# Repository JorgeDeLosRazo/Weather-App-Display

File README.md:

# Weather App Display

### Materials
- Adafruit HUZZAH32 (ESP32 feather)
- 3.7" 416x240 Monochrome Black/White eInk / ePaper - Bare Display (UC8253 Chipset)
- Adafruit eInk Breakout Friend with 32KB SRAM
- 5V 1A phone charger (to connect HUZZAH32 to wall outlet)

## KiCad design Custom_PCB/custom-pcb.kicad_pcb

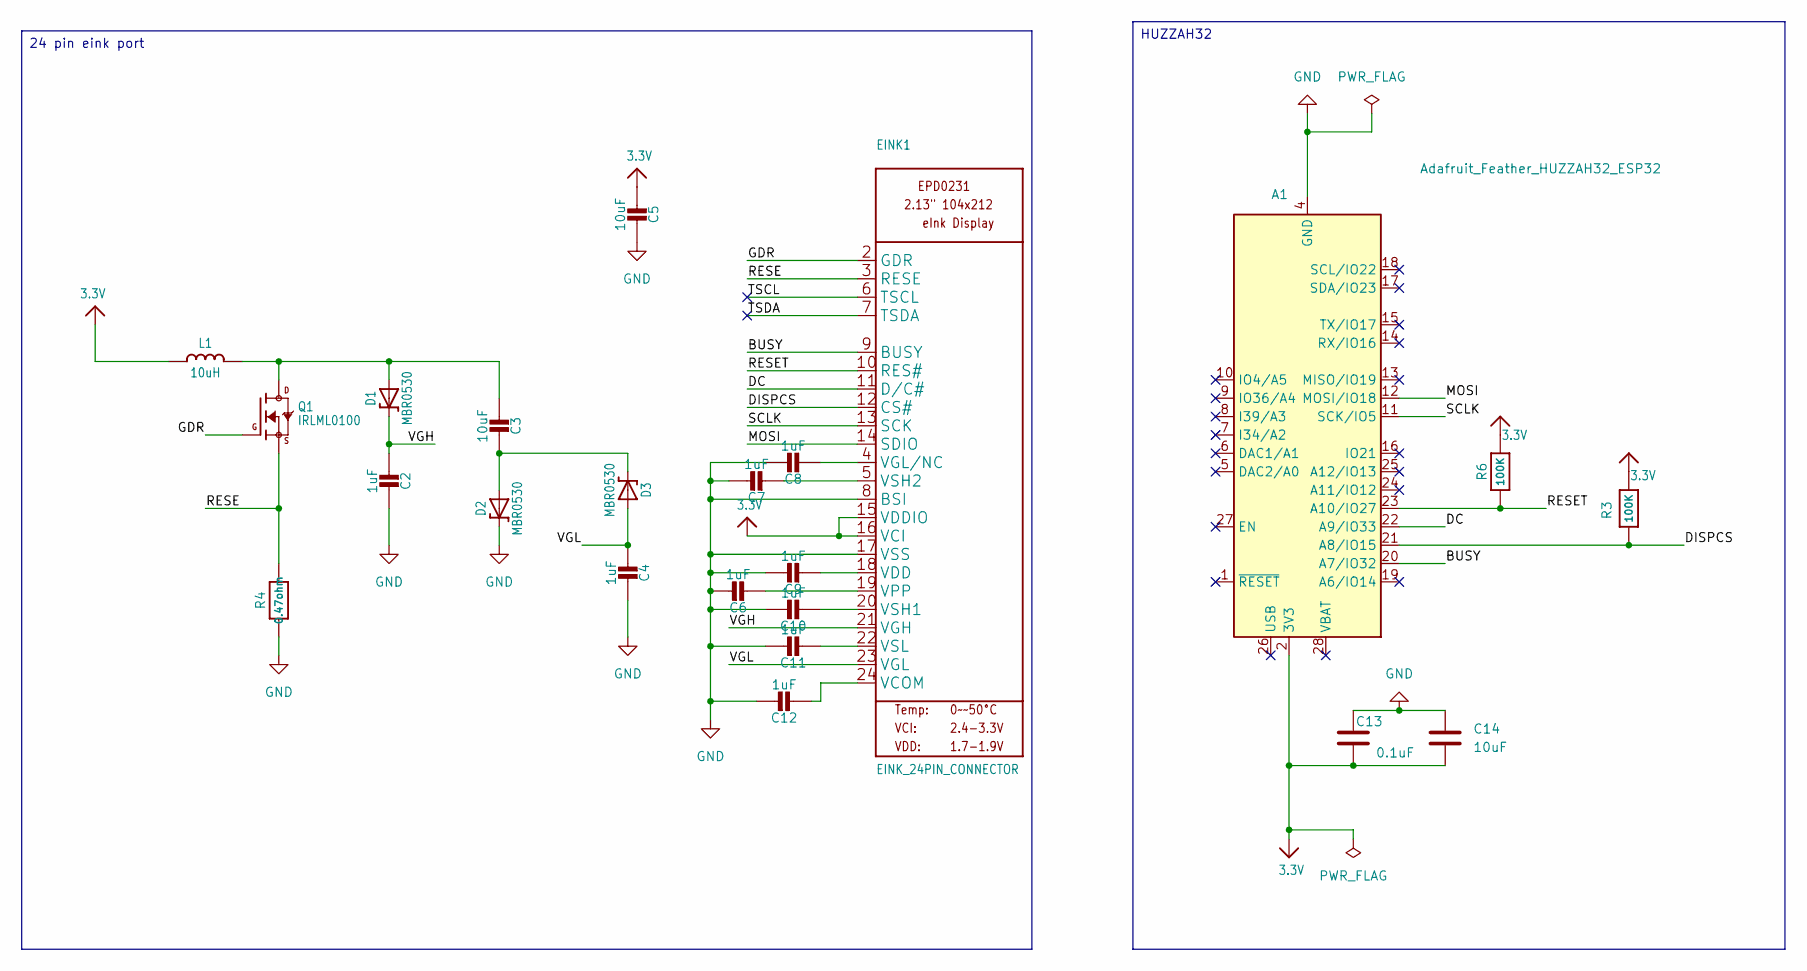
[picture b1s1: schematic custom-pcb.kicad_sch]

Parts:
A1: Adafruit_Feather_HUZZAH32_ESP32; Adafruit_Feather
C2, C4, C6, C7, C8, C9, C10, C11, C12: 1uF; 0805-NO
C3, C5, C14: 10uF; 0805-NO
C13: 0.1uF; 0805-NO
D1, D2, D3: MBR0530; SOD-123
EINK1: EINK_24PIN_CONNECTOR; EINK_24PIN
L1: 10uH; INDUCTOR_4X4MM_NR401
Q1: IRLML0100; SOT23-3
R3, R6: 100K; 0603-NO
R4: 0.47ohm; 0805-NO

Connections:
3.3V: A1.2 (3V3), C5.2, C13.2, C14.2, EINK1.15 (VDDIO), EINK1.16 (VCI), L1.P$2 (2), R3.2, R6.2
/BUSY: A1.20 (A7/IO32), EINK1.9 (BUSY)
/DC: A1.22 (A9/IO33), EINK1.11 (D/C#)
/DISPCS: A1.21 (A8/IO15), EINK1.12 (CS#), R3.1
/GDR: EINK1.2 (GDR), Q1.1 (G)
/MOSI: A1.12 (MOSI/IO18), EINK1.14 (SDIO)
/RESE: EINK1.3 (RESE), Q1.2 (S), R4.1
/RESET: A1.23 (A10/IO27), EINK1.10 (RES#), R6.1
/SCLK: A1.11 (SCK/IO5), EINK1.13 (SCK)
/TSCL: EINK1.6 (TSCL)
/TSDA: EINK1.7 (TSDA)
/VGH: C2.1, D1.C, EINK1.21 (VGH)
/VGL: C4.1, D3.A, EINK1.23 (VGL)
GND: A1.4 (GND), C2.2, C4.2, C5.1, C6.1, C7.1, C8.1, C9.1, C10.1, C11.1, C12.1, C13.1, C14.1, D2.C, EINK1.8 (BSI), EINK1.17 (VSS), R4.2
unnamed: C3.2, D2.A, D3.C
unnamed: C12.2, EINK1.24 (VCOM)
unnamed: C9.2, EINK1.18 (VDD)
unnamed: C8.2, EINK1.4 (VGL/NC)
unnamed: C6.2, EINK1.19 (VPP)
unnamed: C10.2, EINK1.20 (VSH1)
unnamed: C7.2, EINK1.5 (VSH2)
unnamed: C11.2, EINK1.22 (VSL)
unnamed: C3.1, D1.A, L1.P$1 (1), Q1.3 (D)

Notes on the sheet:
24 pin eink port
HUZZAH32

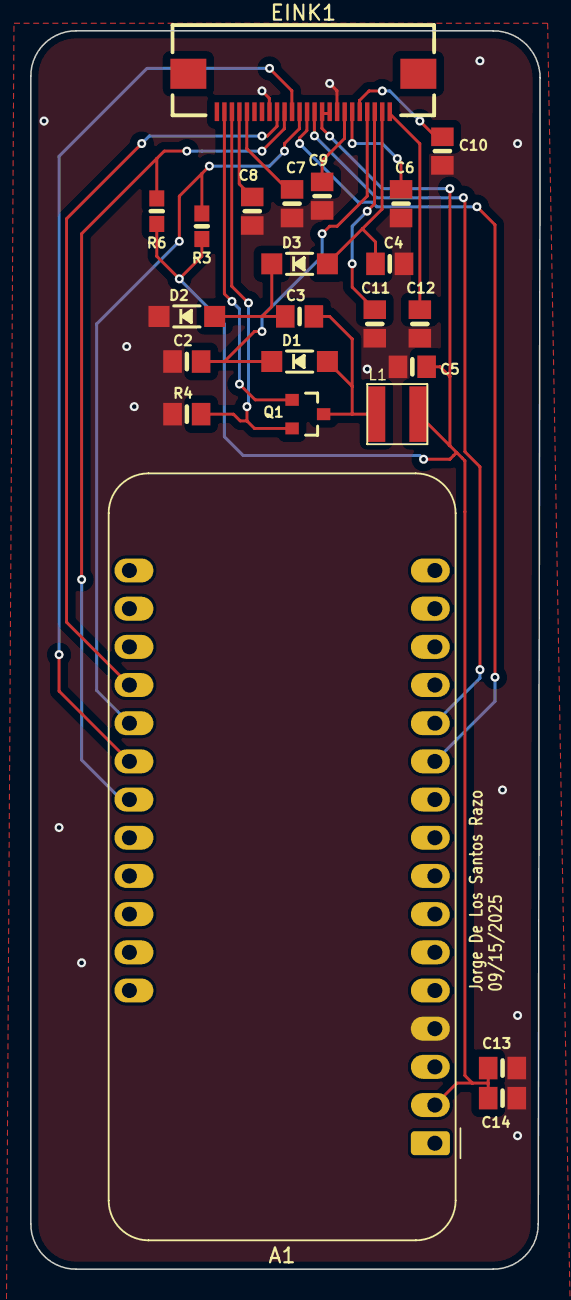
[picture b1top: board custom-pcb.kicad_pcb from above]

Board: 2 copper layers, 33.9 x 82.4 mm, 23 parts (0 on the bottom side), 21 nets.

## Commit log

2025-08-23 Code for display
2025-08-23 added some comments to code
2025-08-24 Added code for wifi connection
2025-08-24 alpha code added
2025-08-25 added code for http request for weather data
2025-08-25 modified alpha code and wifi code
2025-08-26 added some lines to the alpha_code
2025-08-26 display now shows data from http call
2025-08-30 code to get current time to show when display was last updated
2025-08-31 updated alpha code
2025-09-02 added final touches to final code
2025-09-15 changed name of some folders and created a folder for a custom PCB
2025-09-15 gitignore file
2025-09-15 Custom PCB for project
2025-09-15 custom PCB
2025-09-16 removed fiducials
2025-09-21 added a footprint
2025-09-21 small change to schematic
2025-09-30 updated names
2025-09-30 extra stuff
